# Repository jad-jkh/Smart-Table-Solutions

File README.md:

# Smart-Table-Solutions

Sample files from Jad Haddad's Smart Table Solutions including: KiCad PCB files (schematic, layout, and 3D view) and screenshots, along with embedded C code for motor control.

## Overview
Smart Table Solutions provides an automated height-adjustable table control system using an STM32F103C8T6 (Blue Pill) microcontroller and DRV8876 motor driver. The system allows users to adjust table height via simple button controls.

## Hardware Components
- **Microcontroller:** STM32F103C8T6 (Blue Pill)
- **Motor Driver:** DRV8876
- **Buttons:** 2x momentary push buttons (Up/Down control)
- **LED:** Status indicator (reserved for future features)

## Pin Configuration
| Component | Pin | Description |
|--------------|----------|-------------------------------------------|
| Button Down  |   PB12   | Active LOW with internal pull-up          |
| Button Up    |   PB15   | Active LOW with internal pull-up          |
| Motor Enable | (IN1/EN) | PA6 | Enable signal to DRV8876            |
| Motor Phase  | (IN2/PH) | PA5 | Phase/direction control to DRV8876  |
| LED Reserve  |    PB7   | Reserved for future add-on features       |

## Functionality
- **Hold DOWN button (PB12):** Motor drives table downward
- **Hold UP button (PB15):** Motor drives table upward
- **Hold BOTH buttons:** Motor stops (safety feature)
- **Release buttons:** Motor stops

## Software
The embedded firmware is written in C using the Arduino framework with STM32duino support.

### Features
- Simple hold-to-run button logic
- Safety stop when both buttons pressed simultaneously
- 10ms software debouncing
- Reserved LED pin for custom add on

### Code Structure
- `motorControl.ino` - Main control logic for motor operations

## Setup Instructions

### Hardware Setup
1. Connect ST-Link programmer to Blue Pill SWD pins (SWDIO, SWCLK, GND, 3.3V)
2. Solder buttons to PB12 and PB15 with pull-up configuration and LED + controller if applicable
3. Solder DRV8876 motor driver IN1 to PA6, IN2 to PA5
4. Plug jack into female connector

### Software Setup
1. Install [Arduino IDE](https://www.arduino.cc/en/software)
2. Add STM32 board support:
   - Go to **Settings → Additional boards manager URLs**
   - Add: `https://github.com/stm32duino/BoardManagerFiles/raw/main/package_stmicroelectronics_index.json`
3. Install STM32 boards:
   - **Tools → Board → Boards Manager**
   - Search and install **"STM32 MCU based boards"**
4. Select board:
   - **Tools → Board → STM32 boards → Generic STM32F1 series**
   - **Tools → Board part number → BluePill F103C8**
   - **Tools → Upload method → STLink**
5. Open `motorControl.ino` and upload to Blue Pill

## Repository Contents
- `/pcb` - KiCad PCB design files
  - Schematic files
  - PCB layout
  - 3D view renders
- `/firmware` - Embedded C code
  - `motorControl.ino` - Motor control firmware
- `/screenshots` - Project documentation images

## Author
Jad Haddad

## Contact
jadkh6@gmail.com

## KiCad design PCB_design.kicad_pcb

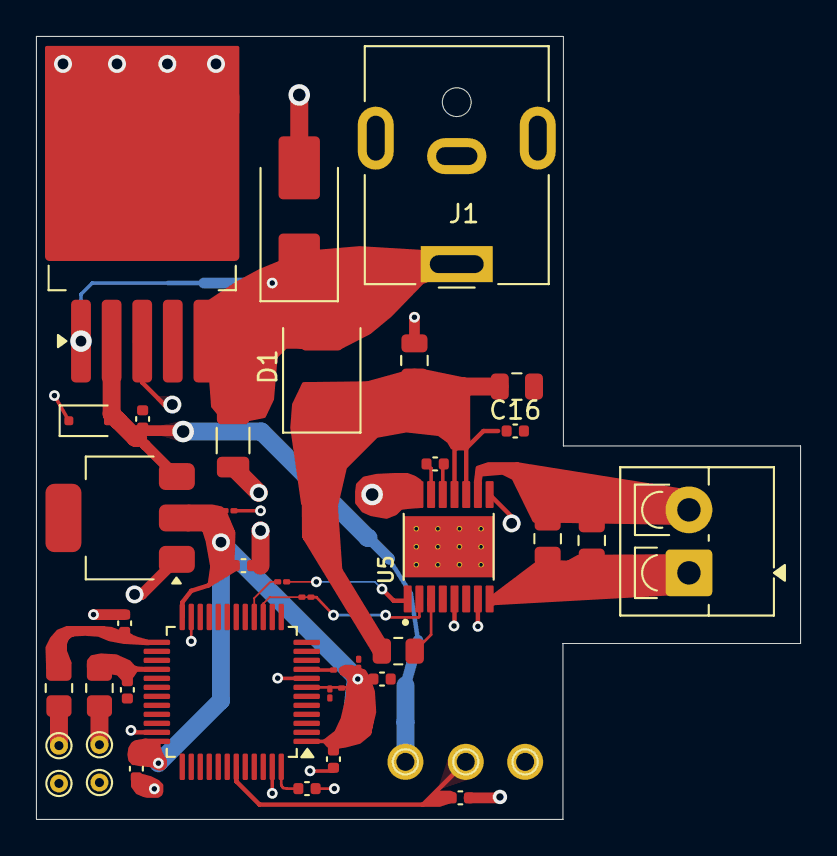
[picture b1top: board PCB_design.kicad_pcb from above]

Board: 2 copper layers, 42.5 x 43.5 mm, 34 parts (0 on the bottom side), 18 nets.

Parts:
C1: 100uF; C_0805_2012Metric
C2, C12: 0.1uF; C_0805_2012Metric
C3: 10uF; C_1206_3216Metric
C4: 10uF; C_0402_1005Metric
C5, C10: 10uF; C_01005_0402Metric
C6: 0.1mF; C_0402_1005Metric
C7, C8, C9, C11, C14, C16, C19, C20, C20#2: 100nF; C_0402_1005Metric
C13: 1nF; C_0805_2012Metric
C15: 10nF; C_01005_0402Metric
D1: SS54; D_SMB
D2: SMBJ18A; D_SMB_Handsoldering
D3: SOD323; D_SOD-323F
J1: Jack-DC; BarrelJack_CUI_PJ-063AH_Horizontal
R1: 10kΩ; R_0805_2012Metric
R2: 10Ω; R_01005_0402Metric
R3: 10kΩ; R_01005_0402Metric
R4, R5: 100Ω; R_01005_0402Metric
R6, R7: 10kΩ; R_0805_2012Metric_Pad1.20x1.40mm_HandSolder
U1: STM32F103C8Tx; LQFP-48_7x7mm_P0.5mm
U2: LM2596S-5; TO-263-5_TabPin3
U3: AMS1117-3.3; SOT-223-3_TabPin2
U5: DRV8876PWPR; IC_DRV8876PWPR

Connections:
BUTTON_DW: C19.2, R6.2, U1.25 (PB12)
BUTTON_UP: C20#2.1, R7.1, U1.28 (PB15)
GND: C1.2, C2.2, C3.1, C4.2, C5.2, C6.1, C7.1, C8.1, C9.1, C10.1, C11.1, C15.1, C16.2, C19.1, C20.1, C20#2.2, D2.2 (A2), D3.1 (A1), J1.2, U1.8 (VSSA), U1.23 (VSS), U1.35 (VSS), U1.47 (VSS), U2.3 (GND), U3.1 (GND), U5.5 (VREF), U5.7 (IMODE), U5.15 (GND), U5.16 (PMODE), U5.17 (EXP)
unnamed: D1.2 (A), D2.1 (A1), J1.1
unnamed: C1.1, C2.1, C16.1, D1.1 (K), R1.2, U5.11 (VM), U5.12 (VCP)
unnamed: C12.1, U5.8 (OUT1)
unnamed: C13.2, U5.10 (OUT2)
unnamed: C15.2, R3.2, U1.7 (NRST)
unnamed: R5.1, R5.2, U1.15 (PA5), U5.2 (PH/IN2)
unnamed: R4.1, R4.2, U1.16 (PA6), U5.1 (EN/IN1)
unnamed: C5.1, C6.2, C7.2, C8.2, C9.2, C10.2, C11.2, R2.1, R3.1, U1.1 (VBAT), U1.24 (VDD), U1.36 (VDD), U1.48 (VDD), U3.2 (VO)
unnamed: R2.2, U1.9 (VDDA)
unnamed: C4.1, D3.2 (A2), U2.2 (OUT)
unnamed: C3.2, U2.1 (VIN), U2.5 (~ON/OFF)
unnamed: C14.1, U5.13 (CPH)
unnamed: C14.2, U5.14 (CPL)
unnamed: R1.1, U5.3 (NSLEEP)
RES IF SWDIO: U1.10 (PA0), U1.11 (PA1)

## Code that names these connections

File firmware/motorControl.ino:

#define DOWN_BTN PB12
#define UP_BTN PB15
#define ENABLE PA6  // EN
#define MOTOR_CONTROL PA5  // PH
#define LED_RESERVE PB7

void setup() {
  // BUTTON PIN CONFIGURATION
  pinMode(DOWN_BTN, INPUT_PULLUP);
  pinMode(UP_BTN, INPUT_PULLUP);
  
  // MOTOR DRIVER PIN OUTPUT
  pinMode(ENABLE, OUTPUT);
  pinMode(MOTOR_CONTROL, OUTPUT);
  
  // RESERVED PIN, THIS TABLE DID NOT USE
  pinMode(LED_RESERVE, OUTPUT);
  
  // MOTOR INITIALIZED STOPPED
  digitalWrite(ENABLE, LOW);
  digitalWrite(MOTOR_CONTROL, LOW);
}

void loop() {

  if (digitalRead(DOWN_BTN) == LOW && digitalRead(UP_BTN) == LOW) {
  // BOTH PRESSED, STOP
  digitalWrite(ENABLE, LOW);
  digitalWrite(MOTOR_CONTROL, LOW);
  }

  // CHECK DOWN BUTTON (active low)
  else if (digitalRead(DOWN_BTN) == LOW) {
    digitalWrite(ENABLE, HIGH);
    digitalWrite(MOTOR_CONTROL, LOW);   // PH = LOW
  }
  // CHECK UP BUTTON (pull high)
  else if (digitalRead(UP_BTN) == LOW) {
    digitalWrite(ENABLE, HIGH);
    digitalWrite(MOTOR_CONTROL, HIGH);  // PH = HIGH
  }
  // No button pressed - Stop
  else {
    digitalWrite(ENABLE, LOW);   // EN = LOW
    digitalWrite(MOTOR_CONTROL, LOW);   // PH = LOW
  }
  
  delay(10);  // DEBOUNCE 10MS
}

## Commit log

2026-02-10 README.md
2026-02-10 Create pcb
2026-02-10 Rename PCB_design.kicad_pcb to pcb/PCB_design.kicad_pcb
2026-02-10 Rename PCB_design.kicad_pro to pcb/PCB_design.kicad_pro
2026-02-10 Rename PCB_design.kicad_sch to pcb/PCB_design.kicad_sch
2026-02-10 Rename motorControl.ino to firmware/motorControl.ino
